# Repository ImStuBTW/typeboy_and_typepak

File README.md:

# The TypeBoy & TypePak

The TypeBoy is a fairly standard split ergonomic keyboard with a very non-standard microcontroller setup. Your eyes don't deceive you: This is a keyboard that needs a Game Boy Advance cartridge to function.

More specifically, it needs a TypePak! I've been spending a lot of time in the Ergogen keyboard layout generator lately, and I recently finished building a Sanni Open Source Cartridge Reader. These two worlds collided in my head and it dawned on me that a keyboard's microcontroller stack could probably fit in the shell of a Game Boy cartridge. A bit of tinkering in KiCAD later, and suddenly this monstrosity the TypePak was born.

## [The TypePak](typepak/README.md)

The TypePak is a keyboard daughterboard with a XIAO nRF52840 Bluetooth microcontroller, a SN74HC595DT shift register, a LS011B7DH03 Sharp Memory Display, and a 401020 lipo battery designed to be housed inside of a standard Game Boy Advance cartridge. Every pin is broken out in case you find some novel use for SPI, or chose not to use the screen. The battery trace and reset pins are also broken out so that you can put a power and reset switch on the main keyboard. You'll need to use a tool similar to a Dremel in order to cut a USB-C port in the side of the cartridge shell.

## [The TypeBoy](typeboy/README.md)

The TypeBoy is a typical split keyboard with a 6x4+5 column staggered layout. The big difference being that it has a 32 pin slot for the Game Boy Advance cartridge. The connector appears on both sides of the board, with traces and vias making the connector pinout reversible. The other notable feature is a SLLB510100 thumb switch.

## [ZMK-Config](/zmk-config)

The ZMK wireless keyboard firmware configuration for this board is relatively standard. The software doesn't have any clue that it's being housed on an odd removable cartridge. Items to note are the LS011B7DH03 display using ZMK's built in Display support instead of the Nice!View wrapper one may be more familiar with, 74HC595 shift register support to add additional column output pins, and a [composite](https://zmk.dev/docs/config/kscan#composite-driver) key scan driver for using both a traditional keyboard matrix and direct pin reading for the thumb wheel.

## Acknowledgements

The TypeBoy isn't the first mechanical keyboard which takes microcontroller cartridges. [mujimanic](https://www.reddit.com/user/mujimanic/)'s [Giga40](https://www.reddit.com/r/MechanicalKeyboards/comments/kut2nk/now_youre_playing_with_power_giga40_power/) keyboard design and it's Famicom cartridges helped prove a low-profile Game Boy-centric version of this idea was worth pursuing.

The TypePak's display connector circuit is based off of [karnadii](https://github.com/karnadii)'s [Sharp Memory Display breakout board](https://github.com/karnadii/sharp_memory_display_breakout) design. The TypePak's PCB is based off of templates from [djedditt](https://github.com/djedditt/)'s [kicad-gamepaks](https://github.com/djedditt/kicad-gamepaks) library. The Game Boy cartridge slot KiCAD footprint was used from [Martin Refseth](https://github.com/HDR)'s [Game Boy KiCad Library](https://github.com/HDR/Game-Boy-KiCad-Library).

As usual, thanks to the [Absolem Club Discord](https://discord.gg/DbCfZfZ) and their #Ergogen channel for answering my endless onslaught of questions. Particularly special thanks to [Pete Johanson](https://github.com/petejohanson) for assisting with some ZMK troubleshooting when the low profile rotary encoders were giving me trouble. The ZMK firmware is heavily influenced by previous configs by [GEIST](https://github.com/GEIGEIGEIST/zmk-config-totem/tree/master/config), [Pete Johanson](https://github.com/petejohanson/zaphod-config/tree/main/boards/shields/zaphod_lite), and [JonMuller](https://github.com/JonMuller/gerbers/tree/main/corne-choc-xiao).

This keyboard is another derivative of [Josef Adamčík](https://josef-adamcik.cz/)'s original [Sofle Keyboard](https://josefadamcik.github.io/SofleKeyboard/) layout. I need to start experimenting with other layouts at this point, but it's hard to beat that thumb cluster.

Finally, another shout out to [GEIST](https://github.com/GEIGEIGEIST), [Freya](https://github.com/freya-irl), [Bubbleology](https://github.com/bubbleology) for their work on the [TOTEM](https://github.com/GEIGEIGEIST/TOTEM) keyboard's case. It was a big inspiration for this build, and they pulled the concept off way better than I did.

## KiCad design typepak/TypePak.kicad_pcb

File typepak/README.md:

# The TypePak

The TypePak is a custom keyboard controller PCB housed inside of an aftermarket Game Boy Advance cartridge shell. It features Bluetooth connectivity, ZMK support, a low-power monochrome display, a built in LiPo battery, 9 GPIO pins, and 8 dedicated output pins. Simply slot the TypePak into a keyboard with a compatible Game Boy cartridge slot, flip the power switch, and you've got yourself a working wireless keyboard. (After flashing the appropriate firmware and keymap, naturally.)

Unlike its companion TypeBoy, the TypePak was designed in KiCAD from scratch. Sadly there aren't any esoteric Game Boy cartridge generators just yet. This repository contains a standard KiCAD project. There's a schematic, a routed PCB, and a Gerber file.

## Layout & Pinout

The heart of the TypePak is a XIAO nRF52840 microcontroller. It handles all of the Bluetooth communication, the wireless battery charging, and USB connectivity. The XIAO "BLE" famously has several pins mounted in the middle of the board on its underside, so the TypePak has several small holes in the PCB to reach the reset, power, and NFC pins.

There's a few additional pieces of hardware mounted onto the board. The TypePak features a LS011B7DH03 Sharp Memory Display. This is the same module found on the Nice!View keyboard display, but instead leverages karnadii's excellent [sharp_memory_display_breakout](https://github.com/karnadii/sharp_memory_display_breakout) circuit design. The microcontroller also takes advantage of a 74HC595 shift register to provide several more output pins. All of this is powered by a 401020 LiPo battery.

A Game Boy cartridge has 32 pins on its edge connector. The XIAO nRF52840 and the shift register have a total of 26 pins. Rather than leave twenty precent of the TypePak's cartridge pins unused, several of the important pins are exposed on both ends of the cartridge's edge connector. The battery output, power pins, reset pins, and a few others are duplicated so that you can more easily route some of the support hardware on your keyboard PCB.

Speaking of which, the TypePak does not have a built in power switch or reset button of its own. (Technically the XIAO does have a reset button, but it's underneath the cartridge's plastic casing.) You'll need to create out these components on the keyboard itself. The whole idea of this setup is to evoke the stylings of a classic Game Boy, so a large chunky power switch is honestly a welcome addition. Just remember, the battery is physically disconnected unless the keyboard's power switch is turned on, so the TypePak can't charge when disconnected from a board.

## Building a TypePak

The TypePak is enclosed inside of an aftermarket Game Boy Advance cartridge. Believe it or not, these cartridges typically did not feature cutouts for USB-C ports. You'll need to drill one into the side of your cartridge so that the TypePak can charge and be flashed with new firmware.

Cutting a hole in the side of the cartridge won't be enough. You'll also need to shave away some of the inside of the top of the case. You should be able to leave most of the exterior of the top untouched. There's *just* enough material on the inside of the case to make everything fit. The cartridge may bow slightly, but you should be able to get all the tabs locked securely into place and the fastener screw fully secured into place. Aftermarket cartridges are fairly cheap, so you may want to buy an extra to practice on.

## Build of Materials

| Part                             | Amount         | Price       | Link |
| -------------------------------- | -------------- | --------------------- | ---- |
| TypePak PCB Via JLCPCB           | 1 (5 PCB Pack) | $2-4.00 USD | https://jlcpcb.com |
| XIAO nRF52840 Microcontroller    | 1              | $10.00 USD  | https://www.digikey.com/en/products/detail/seeed-technology-co-ltd/102010448/16652893 |
| HFK110CT-ND Display Connector    | 1              | $1.35 USD   | https://www.digikey.com/en/products/detail/hirose-electric-co-ltd/FH12A-10S-0-5SH-55/1110331 |
| 560PF Capacitor                  | 2              | $0.15 USD   | https://www.digikey.com/en/products/detail/samsung-electro-mechanics/CL21C561JBANNNC/3887492 |
| 1UF Capacitor                    | 2              | $0.10 USD   | https://www.digikey.com/en/products/detail/samsung-electro-mechanics/CL21B105KBFNNNG/3894467 |
| 300 OHM Ferrite Beads            | 2              | $0.20 USD   | https://www.digikey.com/en/products/detail/vishay-dale/ILBB0805ER301V/2574914 |
| SN74HC595 Shift Register         | 1              | $1.00 USD   | https://www.digikey.com/en/products/detail/texas-instruments/SN74HC595DT/1571266 |
| LS011B7DH03 Sharp Memory Display | 1              | $15.00 USD  | https://www.aliexpress.us/item/3256801622787441.html |
| 401020 LiPo Battery (80 mAh)     | 1              | $7.00 USD   | https://www.amazon.com/gp/product/B09FLX9VZD/ |
| Game Boy Advance Cartridge Shell | 1              | $3.50 USD   | https://www.aliexpress.us/item/3256803793023444.html |

The above table represents the parts needed to construct a single TypePak. You'll need to double everything except for the PCB order if you plan on making two. (JLCPCB fabricates PCBs in groups of 5 as a minimum.) If you're building two TypePaks, it's probably worth bumping the capacitor and ferrite bead orders up to 10. You don't want to have your entire project get stalled if you misplace one of the small components, and the bulk ordering pricing makes buying 4-6 units approximately the same cost as 10.

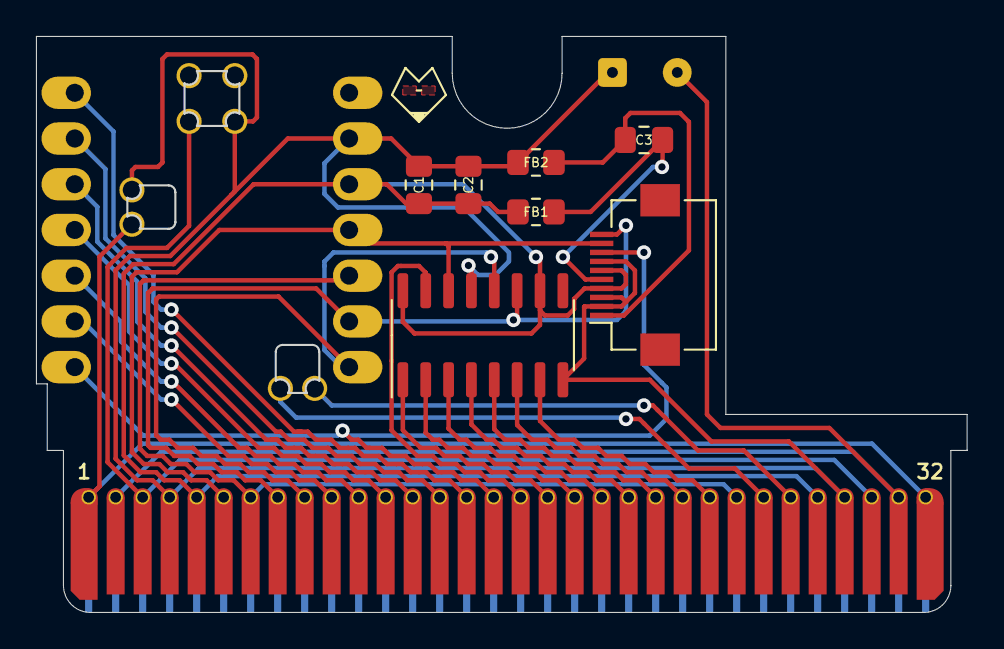
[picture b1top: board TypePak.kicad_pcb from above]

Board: 2 copper layers, 51.6 x 31.9 mm, 10 parts (0 on the bottom side), 28 nets.

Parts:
C1: 560pF/680pF; C_0805_2012Metric_Pad1.18x1.45mm_HandSolder
C2, C3: 1uF; C_0805_2012Metric_Pad1.18x1.45mm_HandSolder
FB1, FB2: FerriteBead_Small; R_0805_2012Metric_Pad1.20x1.40mm_HandSolder
J1: Conn_01x32_Male; GameBoy_GamePak_AGB-002_P1.50mm_Edge
J2: Conn_01x02_Female; SolderWire-0.1sqmm_1x02_P3.6mm_D0.4mm_OD1mm
J3: Conn_01x10; Hirose_FH12-10S-0.5SH_1x10-1MP_P0.50mm_Horizontal
U1: xiao-ble; xiao-ble-smd-cutout-nfc
U2: 74HC595; SOIC-16_3.9x9.9mm_P1.27mm

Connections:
BATIN: J1.2, J1.31, J2.2
BATOUT: J1.1, J1.32, U1.19 (BAT)
GND: C1.2, C2.2, FB2.1, J1.4, J1.29, J2.1, J3.4, J3.8, J3.9, U1.13 (GND), U1.18 (GND), U1.20 (GND), U2.8 (GND), U2.13 (~OE)
IO_CS: J1.9, U1.8 (B9_RX/1.12), U2.12 (RCLK)
LCD_CS: J1.16, J3.3, U1.7 (B8_TX/1.11)
MISO: J1.7, J1.25, U1.10 (A5_MISO/1.14)
MOSI: J1.6, J3.2, U1.11 (A6_MOSI/1.15), U2.14 (SER)
NFC0: J1.26, U1.21 (NFC1/0.09_H)
NFC1: J1.27, U1.22 (NFC2/0.10_H)
unnamed: C3.1, FB1.1, J3.6
unnamed: C3.2, FB2.2, J3.10
RST: J1.3, J1.30, U1.17 (RESET)
SCK: J1.8, J3.1, U1.9 (A7_SCK/1.13), U2.11 (SRCLK)
VCC: C1.1, C2.1, FB1.2, J1.5, J1.28, J3.5, J3.7, U1.12 (3V3), U2.10 (~SRCLR), U2.16 (VCC)
col0: J1.17, U2.15 (QA)
col1: J1.18, U2.1 (QB)
col2: J1.19, U2.2 (QC)
col3: J1.20, U2.3 (QD)
col4: J1.21, U2.4 (QE)
col5: J1.22, U2.5 (QF)
col6: J1.23, U2.6 (QG)
col7: J1.24, U2.7 (QH)
row0: J1.15, U1.1 (A2/0.02_H)
row1: J1.14, U1.2 (A4/0.03_H)
row2: J1.13, U1.3 (A10/0.28)
row3: J1.12, U1.4 (A11/0.29)
row4: J1.11, U1.5 (A8_SDA/0.04_H)
row5: J1.10, U1.6 (A9_SCL/0.05_H)

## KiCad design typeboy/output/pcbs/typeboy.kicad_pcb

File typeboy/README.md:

# The TypeBoy

The TypeBoy is a four row, six column, five modifier column staggered split ergonomic keyboard. A 6x4+5 layout as the cool kids would say. Stop me if you've heard this one before, but it was inspired by [Josef Adamčík](https://josef-adamcik.cz/)'s [Sofle keyboard](https://josefadamcik.github.io/SofleKeyboard/).

This keyboard was designed mostly as a testbed for the TypePak microcontroller cartridge. It doesn't have too much going on outside of the Game Boy slot on the side. The only other peculiar hardware feature is the SLLB510100 thumb switch. It's a low profile slide switch that you can rotate to the left or right as well as pushing straight in. It's similar in purpose to a rotary encoder, but it just rocks back and forth instead of spinning. If you used a CD player around the turn of the century you probably know what to expect.

## Ergogen Outputs

It should come as no surprise that I leveraged [Ergogen](https://github.com/ergogen/ergogen) to design the TypeBoy. The ergonomic keyboard generator makes it easy to turn keyboard concepts into full fledged designs. I wrote a whole blog post about it if you’re interested.

The TypeBoy uses several custom footprints. Most notably, the large Game Boy cartridge slot. To use these config files, clone this repository and install Ergogen onto your local system. Browse to this TypeBoy folder and run `ergogen .`to process `config.yaml`.

The primary output is the TypeBoy PCB. Ergogen will create an unrouted KiCAD file, but I’ve gone ahead and included the fully routed board in the repository. The resulting Gerber files are also included if you want to run the board off without any modifications.

Ergogen also has the ability to output vector outline files or 3D case files. The TypeBoy’s config outputs several outlines, but the case design I had in mind for this board were a little too complicated tor Ergogen itself. I ended up building the TypeBoy’s case in AutoDesk Fusion 360.

There’s one unusual output Ergogen produces in this design. It makes a “backplate” PCB. This is a bit of an unusual concept I’ve experimented with for my last few builds. It’s loosely based off the [Horizon](https://github.com/skarrmann/horizon) keyboard, with the intention of providing cutouts for diodes and footprint switches when building a case.

Unlike the Horizon, I just export the PCB design as a `.step` file and then use an online tool to convert the file into a `.stl` file I can e corporate into a 3D printed case design. The end result is a bottom piece that perfectly fits the components without providing a lot of echo-y blank space.

The case output folder has three files. The bottom pieces aren’t symmetrical. (The hotswap sockets aren’t flipped.) The top piece is symmetrical, so you can just flip it in your 3D printing software of choice before sending it though. The top and bottom pieces use seven M2 heat set screw inserts.

## Additional Footprints

Ergogen v4 supports custom footprints! The TypeBoy colors outsides the lines and includes a few not included in the standard repo:

* buttonrightangle.js - A right angle pushbutton.
* gbareversible.js - A reversible game boy cartridge slot footprint based off of [Martin Refseth's KiCAD footprint](https://github.com/HDR/Game-Boy-KiCad-Library/blob/master/Footprints/DSL_Cartridge_Reader.kicad_mod).
* lowproro.js - A footprint for the SIQ-02FVS3 low profile rotary encoder. Used in an earlier TypeBoy design.
* lowprothumb.js - A footprint for the SLLB510100 thumb switch used on later TypeBoy builds.
* mountinghole.js - An M2 mounting hole footprint.

There's also several "backplate" footprints. These are footprints which just have an edge cut drawn around the space where the standard component goes. `diode.js` handles the diodes, `diodebackplate.js` handles the cutout. Etc. Creating these as footprints rather than Ergogen outlines makes it a bit easier to place each backplate cutout exactly where the corresponding component goes.

## Build of Materials

| Part                             | Amount         | Price       | Link |
| -------------------------------- | -------------- | --------------------- | ---- |
| TypeBoy PCB Via JLCPCB           | 1 (5 PCB Pack) | $20.00 USD (Incl. Slow Shipping) | https://jlcpcb.com |
| Game Boy Cartridge Slot          | 2              | $5.00 USD  | https://www.aliexpress.us/item/2255800103876564.html |
| SLLB510100 Thumb Switch          | 2              | $8.00 USD   | https://www.mouser.com/ProductDetail/Hirose-Connector/FH12A-10S-0.5SH55 |
| Right Angle Pushbutton           | 2              | $1.00 USD   | https://www.mouser.com/ProductDetail/642-MJTP1117 |
| Right Angle Switch               | 2              | $1.50 USD   | https://www.mouser.com/ProductDetail/612-EG1213 |
| Choc Hotswap Sockets             | 58             | $12.00 USD  | https://www.aliexpress.us/item/3256803687338432.html |
| 1N4148 T4 Diodes                 | 58             | $3.00 USD   | https://www.aliexpress.us/item/2255800498728983.html |
| Choc Switches                    | 58             | $28.00 USD  | https://www.aliexpress.us/item/3256805260407528.html |
| Choc Keycaps                     | Alphas + Mods  | $~60.00 USD | https://mkultra.click/mbk-legend-keycaps/ |
| 3D Printed Case                  | Buy Your Buddy Some Filament | $~20.00 USD | https://github.com/ImStuBTW/typeboy_and_typepak/tree/main/typeboy/output/case |
| Bumpons                          | 1 Pack  | $10.00 USD | https://www.amazon.com/Adhesive-Bumper-106-PC-Spherical-Square/dp/B06XPCLN23/ |

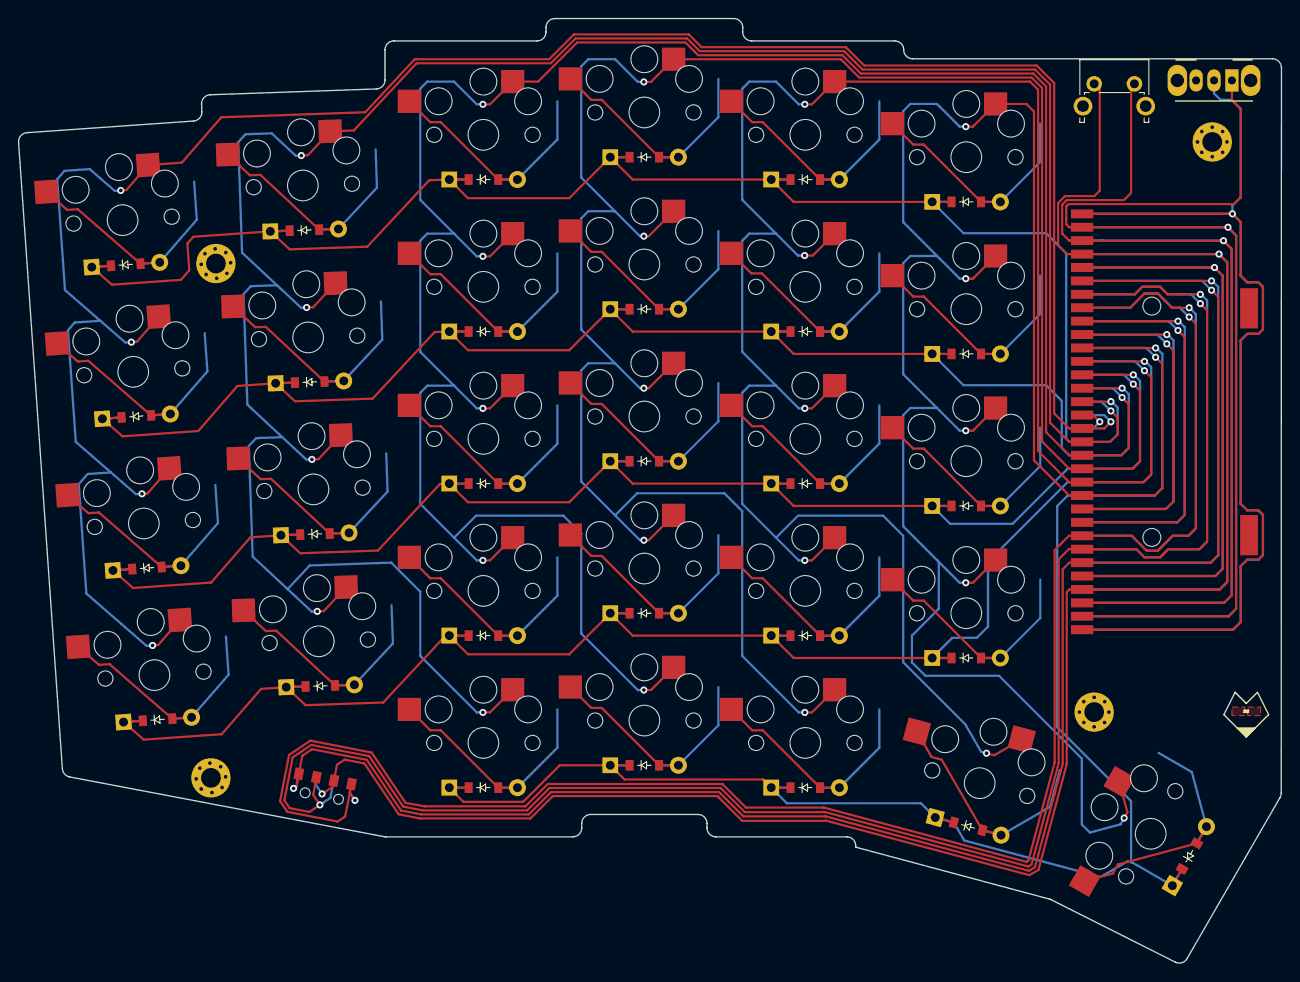
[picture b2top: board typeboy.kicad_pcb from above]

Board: 2 copper layers, 141.2 x 105.6 mm, 64 parts (0 on the bottom side), 55 nets.

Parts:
D1, D2, D3, D4, D5, D6, D7, D8, D9, D10, D11, D12, D13, D14, D15, D16, D17, D18, D19, D20, D21, D22, D23, D24, D25, D26, D27, D28, D29: ComboDiode
J2: CartBus; GBA_Reversible_Cart_Reader
S1, S2, S3, S4, S5, S6, S7, S8, S9, S10, S11, S12, S13, S14, S15, S16, S17, S18, S19, S20, S21, S22, S23, S24, S25, S26, S27, S28, S29: PG1350
S**: SLLB510100
_1, _2, _3, _4: MountingHole_2.2mm_M2_Pad_Via

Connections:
BATIN: J2.2, J2.31, J2.34, J2.63
BATOUT: J2.1, J2.32, J2.33, J2.64
GND: J2.4, J2.29, J2.36, J2.61, S**.C1, S**.T1
IO_CS: J2.9, J2.56
LCD_CS: J2.16, J2.49
MISO: J2.7, J2.25, J2.40, J2.58, S**.1
MOSI: J2.6, J2.59
NFC0: J2.26, J2.39, S**.C1, S**.T1
NFC1: J2.27, J2.38, S**.2
RST: J2.3, J2.30, J2.35, J2.62
SCK: J2.8, J2.57
VCC: J2.5, J2.28, J2.37, J2.60
col0: J2.17, J2.48, S1.1, S2.1, S3.1, S4.1
col1: J2.18, J2.47, S5.1, S6.1, S7.1, S8.1, S9.1
col2: J2.19, J2.46, S10.1, S11.1, S12.1, S13.1, S14.1
col3: J2.20, J2.45, S15.1, S16.1, S17.1, S18.1, S19.1
col4: J2.21, J2.44, S20.1, S21.1, S22.1, S23.1, S28.1
col5: J2.22, J2.43, S24.1, S25.1, S26.1, S27.1, S29.1
col6: J2.23, J2.42
col7: J2.24, J2.41
index_bottom: D20.2, S20.2
index_home: D21.2, S21.2
index_mod: D19.2, S19.2
index_num: D23.2, S23.2
index_top: D22.2, S22.2
inner_bottom: D24.2, S24.2
inner_home: D25.2, S25.2
inner_num: D27.2, S27.2
inner_top: D26.2, S26.2
layer_cluster: D28.2, S28.2
middle_bottom: D15.2, S15.2
middle_home: D16.2, S16.2
middle_mod: D14.2, S14.2
middle_num: D18.2, S18.2
middle_top: D17.2, S17.2
outer_bottom: D1.2, S1.2
outer_home: D2.2, S2.2
outer_num: D4.2, S4.2
outer_top: D3.2, S3.2
pinky_bottom: D5.2, S5.2
pinky_home: D6.2, S6.2
pinky_num: D8.2, S8.2
pinky_top: D7.2, S7.2
ring_bottom: D10.2, S10.2
ring_home: D11.2, S11.2
ring_mod: D9.2, S9.2
ring_num: D13.2, S13.2
ring_top: D12.2, S12.2
row0: D4.1, D8.1, D13.1, D18.1, D23.1, D27.1, J2.15, J2.50
row1: D3.1, D7.1, D12.1, D17.1, D22.1, D26.1, J2.14, J2.51
row2: D2.1, D6.1, D11.1, D16.1, D21.1, D25.1, J2.13, J2.52
row3: D1.1, D5.1, D10.1, D15.1, D20.1, D24.1, J2.12, J2.53
row4: D9.1, D14.1, D19.1, D28.1, D29.1, J2.11, J2.54
row5: J2.10, J2.55
space_cluster: D29.2, S29.2

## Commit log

2023-06-17 Switched to `col2row`.
2023-06-21 Encoder Testing.
2023-08-14 Updated Documentation.
2023-08-17 Added Imagery
2023-08-17 Swapped .png for .jpg
2023-08-17 Testing Image Embeds
2023-08-18 Hyperlinks in the Readme
2023-08-18 Added Images To READMEs.
2023-08-18 Fixed Images.
2023-08-18 Build of Materials
2023-08-19 Spelling.
2023-11-11 Fixed Shift Register Link
